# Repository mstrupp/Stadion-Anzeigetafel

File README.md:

# Stadion-Anzeigetafel

## Zusammenfassung

Bei Leichtathletik Wettkämpfen erfolgt die Zeitmessung mit einer elektronischen Zeitmessanlage.
Der Startschuss startet die Stoppuhr und ein Zielbildauswerter bestimmt auf den Zielbildern die Zeiten der Läufer.

Während den Rennen wird auf einer Anzeigetafel die verstrichene Zeit dargestellt.
Außerdem können darauf nach einem Rennen die Zeiten der Läufer angezeigt werden.

In diesem Projekt wird eine Anzeigetafel entwickelt, die mit Zeitmesssystemen der Marke OMEGA kompatibel ist.
Die Anzeige kann eigenständig oder unterstützend eingesetzt werden.
Im eigenständigen Aufbau übernimmt sie alle Aufgaben der Anzeigetafel.
Im unterstützenden Modus werden Zusatzinformationen, wie der Name des Läufers, angezeigt, während eine weitere Anzeigetafel die Zeiten einblendet.

## Technische Daten

Die Namen-Anzeigetafel ist ein LED-Display, das bis zu 12 Buchstaben in einer Zeile anzeigen kann.
Es ist aus einer Distanz von bis zu 75 m lesbar.
Der Benutzer kann zwischen verschiedenen Modi wählen, um den Namen, die Bahn oder die Platzierung anzuzeigen.
Die Helligkeit der Anzeige wird automatisch an die aktuellen Lichtverhältnisse angepasst.
Das regensichere Gehäuse schützt die Elektronik auch bei schlechtem Wetter mit der Schutzklasse IP24.

## Aufbau

### LED Anzeige

Das Display besteht aus einer LED-Matrix.
Dafür werden individuell adressierbare LED-Streifen verwendet. Die LED-Streifen haben eine Dichte von 60 LEDs pro Meter.
Der Pixel-Abstand beträgt etwa 1,7 cm.
Die Anzeige hat eine Auflösung von 83 x 10 Pixeln.
Die Maße der Anzeige betragen etwa 140 x 17 cm.
Jeder Buchstabe ist damit 6 x 10 Pixel bzw. 10 cm x 17 cm groß.

### Mikrocontroller

Die Ergebnis-Daten werden von einem STM Mikrocontroller auf einem Nucleo-32 Board empfangen und aufbereitet.
Die Daten werden von der Zielbildauswertung über die serielle RS422 Schnittstelle bereitgestellt.
Der Mikrocontroller berechnet unter den gegeben Benutzer-Einstellungen die Steuerungssignale für das Display.

### Schnittstellen

Für den Daten-Empfang wird der Data-Out Anschluss der OMEGA-Anzeigetafel verwendet.
Die Verbindung erfolgt über ein Datenkabel mit einem siebenpoligem Tuchel-Anschluss.
Zum Programmieren des Mikrocontrollers ist außerdem ein USB Anschluss am Gehäuse angebracht.

### Automatische Helligkeitsregulierung

Die Helligkeit der Anzeige wird automatisch an die aktuellen Lichtverhältnisse angepasst.
Zur Ermittlung der Umgebungshelligkeit wird ein Fotowiderstand eingesetzt.
Bei starker Sonneneinstrahlung wird zur verbesserten Lesbarkeit die Helligkeit des Displays erhöht.
Bei Dunkelheit wird die Helligkeit verringert.

### Betriebsmodi

Die Anzeigetafel verfügt über verschiedene Betriebsarten.
Es kann entweder der Name oder die Startnummer und die Bahn angezeigt werden.
Über Schalter kann der Bediener auswählen, was angezeigt wird. Ein weiterer Schalter aktiviert das Scrollen von langen Namen, die nicht mit zehn Zeichen dargestellt werden können.
Über ein Potentiometer kann die Helligkeit manuell justiert werden.
Das Ein- und Ausschalten des Geräts ist ebenfalls über einen Schalter möglich.

### Spannungsversorgung

Sowohl der Arduino als auch die LED Streifen benötigen eine elektrische Spannung von 5 V. Diese wird über ein externes Netzteil bereitgestellt.

### Gehäuse

Das Gehäuse besteht aus PVC und bietet damit Schutz vor Regen in der Sicherheitsklasse IP24.
Die Vorderseite besteht aus einer dunklen Plexiglas Scheibe, um die gute Lesbarkeit der Anzeige zu ermöglichen.

## Schaltplan

Zum Einstellen des Modus werden Kippschalter, Potentiometer und Drehschalter verwendet.
Außerdem ermitteln Sensoren die Helligkeit und Temperatur.
Die Komponenten werden auf einer Platine mit dem Mikrocontroller und miteinander verbunden.

[Schaltplan](PCB-Eagle/Anzeigetafel-Schaltplan.pdf)

[PCB](PCB-Eagle/Anzeigetafel-PCB.pdf)

## Steuerung der Anzeige

Die Anzeige besteht aus einer LED-Matrix mit 840 RGB LEDs. Die LEDs sind in Reihen auf LED-Streifen angebracht. Jede einzelne RGB LED besteht aus drei kleinen LEDs in den Farben Rot, Grün und Blau. Durch Kombination der einzelnen Farb-LEDs kann ein breites Farbspektrum erzeugt werden.

### WS2812B RGB LED Streifen

Auf den LED-Streifen sind WS2812B ICs angebracht, die die einzelnen LEDs steuern. Alle ICs sind in Reihe geschaltet. Vom Mikrocontroller werden nacheinander die Farbcodes für die einzelnen LEDs gesendet.

Der erste Chip empfängt das Steuersignal und verarbeitet den ersten Farbcode. Daraufhin enterfernt der IC den ersten Farbcode aus dem Steuersignal und gibt das resultierene Signal an die folgenden Chips weiter.
Die nächsten ICs wiederholen das Vorgehen. Somit wird das Steuersignal von Chip zu Chip kürzer, bis es den letzten Chip erreicht. Am Ende des Steuersignals wird ein Reset-Signal gesendet [3].

Abbildung: Ablauf der WS2812B Steuerung

### Benötigte Signale

Jeder Farbcode besteht aus 24 Bit beziehungsweise 3 Byte. In jedem Byte ist die Intensität einer Farbe enthalten. Im ersten Byte ist der Grünwert, im zweiten der Rotwert und im dritten Byte der Blauwert kodiert. Daraus entstehen drei Werte, die von 0 bis 256 reichen. Diese ergeben den RGB-Wert der LED [3].

Abbildung: Aufbau eines Farbcodes

Die 24 Bit je Farbcode werden elektrisch über ein Datenkabel an die Chips gesendet. Die Spannung auf dem Kabel wird entweder auf "high" oder "low" gesetzt (3,3 V oder 0 V). Je nachdem, wie lange das Signal im Zustand "high" und "low" verbringt, wird es als "0" oder "1" interpretiert. Die genauen Zeitverhältnisse sind in folgender Abbildung dargestellt [3].

Abbildung: Timing der Signale

Die Periode für das Senden einer 0/1-Signals beträgt 1,25 µs. Die high/low-Signale haben eine Toleranz von ±150 ns.

Nachdem die Farbcodes aller LEDs gesendet wurden, folgt ein Reset-Signal. Dazu wird die Datenleitung für mindestens 50 µs auf "low" gebracht [3].

### Erzeugung der Signale

Der Mikrocontroller verfügt über verschiedene Timer. Ein Timer mit PWM (Pulsweitenmodulation) Unterstützung wird für die Erzeugung der Steuersignale verwendet [2].

Die PWM-Periode muss wie gefordert auf 1,25 µs, was einer Frequenz von 800 kHz entspricht, gestellt werden.
Der Timer arbeitet mit einer Frequenz von 64 MHz.
Wenn der Timer innerhalb von einer Periode von 0 bis 79 zählt und dann zurückgesetzt wird, kann die erforderliche Frequenz erreicht werden.

Durch Einstellen des Tastgrades / Duty Cycles kann das Verhältnis von "high" und "low" innerhalb einer Periode geändert werden.

Bei einem Tastgrad von a = 0,32 wird ein "0"-Signal und bei einem Tastgrad von a = 0,64 ein "1"-Signal erzeugt.

#### Direct Memory Access

Der Tastgrad muss also ständig geändert werden.
Wenn die CPU dafür benutzt wird, kann nicht sichergestellt werden, dass das Timing eingehalten wird.
Es würde alle 1,25 µs ein gespeicherter Tastgrad-Wert geladen und ins Timer Register geschrieben werden.
Außerdem ist die CPU somit während dem Senden eines Signals durchgehend ausgelastet und kann nicht auf andere Signale reagieren.

Deshalb wird die DMA (Direct Memory Access) Funktion des Mikrocontrollers eingesetzt.
Diese schafft eine direkte Verbindung zwischen den Speicheradressen der Tastgrade und dem PWM Registers des Timers.
Die CPU startet zu Beginn die DMA-Verbindung.
Dann wird automatisch nach jeder Timer Periode der neue Tastgrad eingestellt [2].

Abbildung: Skizze Direct Memory Access

### Double Buffering

Insgesamt besitzt die Anzeigetafel 840 Pixel.
Wie beschrieben bekommt jeder Pixel ein 24 Bit langes Datensignal.
Für jedes Bit muss der Tastgrad angepasst werden.
Die Tastgrade werden in einem Array gespeichert und dann per DMA an den Timer gegeben.
In dem Array wird jeder Wert als `uint8_t` gespeichert und belegt somit 1 Byte des RAMs.

Das bedeutet, dass das Array eine Speichergröße von 840 * 24 Byte = 20,16 Kilobyte beansprucht.
Das übersteigt die Größe des RAMs des Mikrocontrollers (8 Kilobyte) bei weitem.

Double Buffering wird eingesetzt, um den Speicherbedarf stark zu verringern [4].

Statt ein Array mit allen Tastgraden anzulegen, wird lediglich ein Array mit 48 Einträgen erzeugt.
Dieses bietet Platz für die Tastgrade von genau zwei LEDs.

Der DMA wird im "Circle Mode" konfiguriert.
In diesem Modus sendet er das angegebene Array and die ausgewählte Peripherie und startet dann von vorne.

Dieses Verhalten wird ausgenutzt, um alle LEDs mit dem 48 Byte großen Array anzusteuern.
Zuerst werden die Tastgrade für LED 1 und LED 2 in das Array geladen und der DMA gestartet.
Sobald das Signal für LED 1 generiert wurde, beginnt der DMA, die Tastgrade für LED 2 weiterzugeben.
Währenddessen werden die Tastgrade für LED 1 mit den Tastgraden für LED 3 überschrieben.
Wenn LED 2 gesendet wurde, beginnt der DMA von vorne.
In der ersten Hälfte des Arrays stehen nun die Tastgrade für LED 3 und dadurch wird das dazugehörige Signal generiert.
Das Vorgehen wird wiederholt, bis die Signale für alle LEDs gesendet wurden [4].
Zuletzt wird der Tastgrad auf "0" gesetzt, um das Reset-Signal zu erzeugen.

Abbildung: Ablauf des DMA mit Double Buffering

Der DMA löst Interrupts aus, über die das Tastgrade-Array dann angepasst werden kann.
Wenn die erste Hälfte des Arrays gesendet wurde, wird die Funktion `HAL_TIM_PWM_PulseFinishedHalfCpltCallback` aufgerufen.
Wenn die zweite Hälfte des Arrays gesendet wurde, wird `HAL_TIM_PWM_PulseFinishedCallback` aufgerufen [1].
In diesen Funktionen kann dann das Array mit den neuen Tastgraden befüllt werden.

Abbildung: Auslösen der Interrupts/Callbacks

Die CPU wird beim DMA mit Double Buffering alle 30 µs verwendet.
Damit wird sie 24 Mal weniger belastet als beim Vorgehen ohne DMA.

Das Tastgrade-Array beinhaltet 48 32-Bit Zahlen.
Die Speichergröße beträgt damit 192 Byte.
Dabei spielt es keine Rolle, wie viele LEDs angesteuert werden.
Somit wird im Vergleich zum DMA ohne Double Buffering nur ein Hundertstel des Speicherplatzes verwendet.

## Programm-Repräsentation der LED-Matrix

Um die Verkabelung zu vereinfachen, sind die LEDs im Zickzack auf der Anzeigetafel aufgebrahcht.
In der ersten Zeile läuft das Datensignal daher von links nach rechts, in der zweiten von rechts nach links und so weiter.
Jeder LED wird ein Index, beginnend bei 0, zugeordnet.

Im Programm werden die Farbwerte aller LEDs in einem Array gespeichert.
Die Indizierung unterscheidet sich dadurch in jeder zweiten Zeile, wie in der folgenden Abbildung dargestellt.

Abbildung LED-Matrix und Array Indizierung

Wie zu sehen ist, unterscheiden sich die Indizierung der realen LED-Matrix und die des Arrays in jeder zweiten Zeile.
Um die Buchstaben und Zahlen trotzdem lesbar anzuzeigen, muss der Programmcode entsprechend angepasst werden.

### Programm eines Buchstaben, einer Zahl oder anderen Zeichens

Jedes Zeichen, das angezeigt werden soll, besteht aus einer Matrix.
Diese gibt an, welche LEDs für dieses Zeichen an- und ausgeschaltet werden sollen.

```C
const Character char0x41 = { // A
        .width = 6,
        .height = 10,
        .matrix = {
                0, 0, 1, 1, 0, 0,
                0, 1, 0, 0, 1, 0,
                1, 0, 0, 0, 0, 1,
                1, 0, 0, 0, 0, 1,
                1, 0, 0, 0, 0, 1,
                1, 1, 1, 1, 1, 1,
                1, 0, 0, 0, 0, 1,
                1, 0, 0, 0, 0, 1,
                1, 0, 0, 0, 0, 1,
                1, 0, 0, 0, 0, 1
        }
};
```

Listing: Code für den Buchstaben A

### Programm zum Füllen der LED-Matrix

Folgender Code wird dann zum Füllen des Arrays verwendet.

```C
// Set a character at the current cursor position in the given color.
void LEDMatrixSetCharacter(LEDMatrix* ledMatrix, const Character* character, Color color) {
    int currentCursorPos;;
    // Iterate over all character cells
    for (int line = 0; line < character->height; ++line) {
        currentCursorPos = ledMatrix->cursorPos;
        for (int col = 0; col < character->width; ++col) {
            // Check if the column is inside the matrix
            if (currentCursorPos >= 0 && currentCursorPos < ledMatrix->numCols) {
                // Even line: LEDs from left to right
                if (line % 2 == 0) {
                    ledMatrix->leds[line * ledMatrix->numCols + col + ledMatrix->cursorPos].color =
                            character->matrix[line * character->width + col] ? color : off;
                // Uneven line: LEDs from right to left
                } else {
                    ledMatrix->leds[line * ledMatrix->numCols + (ledMatrix->numCols - 1 - col) - ledMatrix->cursorPos].color =
                            character->matrix[line * character->width + col] ? color : off;
                }
            }
            currentCursorPos += 1;
        }
    }
}
```

Listing: Code zum Hinzufügen eines Buchstaben zur Matrix

An die Funktion werden die LED-Matrix, das neue Zeichen und die Farbe übergeben.
Es wird über jede Zelle der Buchstaben-Matrix iteriert.
Wenn die berechnete Zelle innerhalb der LED-Matrix liegt, wird die zugehörige LED angeschaltet.
Mithilfe von `if (line $ 2 == 0)` wird getestet, ob die Zeile gerade oder ungerade ist.
Wie zuvor beschrieben wird dementsprechend die Beschreibe-Richtung der LED-Matrix angepasst.
Beim Setzen der LED wird dann außerdem die Farbe dieser LED festgelegt.

### Animationen

Unter Benutzung eines weiteren Timers ist es möglich, Animationen auf der Anzeigetafel abzuspielen.
Der Quellcode dafür befindet sich im Ordner `animations`.
Die Animation `SwipeClearAnimation` lässt zum Beispiel einen Streifen von links nach rechts über die Anzeige wischen, der dabei all Zeichen löscht.

Bei Animationen ist zu beachten, dass die Aktualisierungsrate der Anzeige von der Anzahl der LEDs abhängt.
Die Signallänge jedes Bits 1,25 µs.
Für jede LED werden 24 Bit gesendet.
Nach dem Senden aller LED-Signale folgt ein Reset-Puls mit einer Dauer von 50 µs.
Die benötigte Zeit zum Senden eines gesamten Bildes ergibt sich damit zu

`T = n * 24 * 1,25 µs + 50 µs`,
wobei `n` die Anzahl der LEDs ist.

Für die im Projekt verwendeten n = 830 LEDs ergibt sich damit eine Sendezeit von 24,95 ms.
Damit liegt die theoretisch mögliche Aktualisierungsrate bei etwa 4 Bildern pro Sekunde.

## Empfang der Daten

Die Anzeige-Befehle werden über die RS422 Schnittstelle bereitgestellt.
Der MAX485 IC leitet die Daten als für den Mikrocontroller lesbares Signal weiter.
Es gibt verschiedene Protokolle, in denen die Informationen empfangen werden können.
Das Projekt unterstützt das Gemini sowie das Rollertime Protokoll.
Die Dekodierunds-Funktionen sind in den Quelldateien im Ordner `protocols` implementiert.

In den Dekodierungs-Funktionen werden die empfangenen Daten anylisert und geprüft, um welchen Datentyp es sich handelt.
Im Gemini Protokoll kann zum Beispiel enthalten sein:

- Aktuelle Zeit
- Name eines Athleten
- Ergebnis eines Athleten
- Startnummer eines Athleten
- Bahn eines Athleten
- Platzierung eines Athleten
- Clear-Kommando

Je nach empfangenem Signal wird dann entschieden, was auf der Anzeige dargestellt werden soll und die LED-Signale generiert und versendet.

## Gamma Korrektur

```text
corrected = ((value / 255) ^ gamma) * 255
```

Als Gamma Wert wird 2,5 benutzt.

## Referenzen

[1] STMicroelectronics, Description of STM32G0 HAL and low-layer drivers - User manual. 10-2020.

[2] STMicroelectronics, STM32G0x1 advanced Arm®-based 32-bit MCUs - Reference manual. 11-2020.

[3] Worldsemi, WS2812B Datenblatt. 2021.

[4] M. Tilen, “Tutorial: Control WS2812B leds with STM32,” 2018-06-03. <https://stm32f4-discovery.net/2018/06/tutorial-control-ws2812b-leds-stm32/>

[5] Maxim Integrated, MAX485 Datenblatt. 9-2014.

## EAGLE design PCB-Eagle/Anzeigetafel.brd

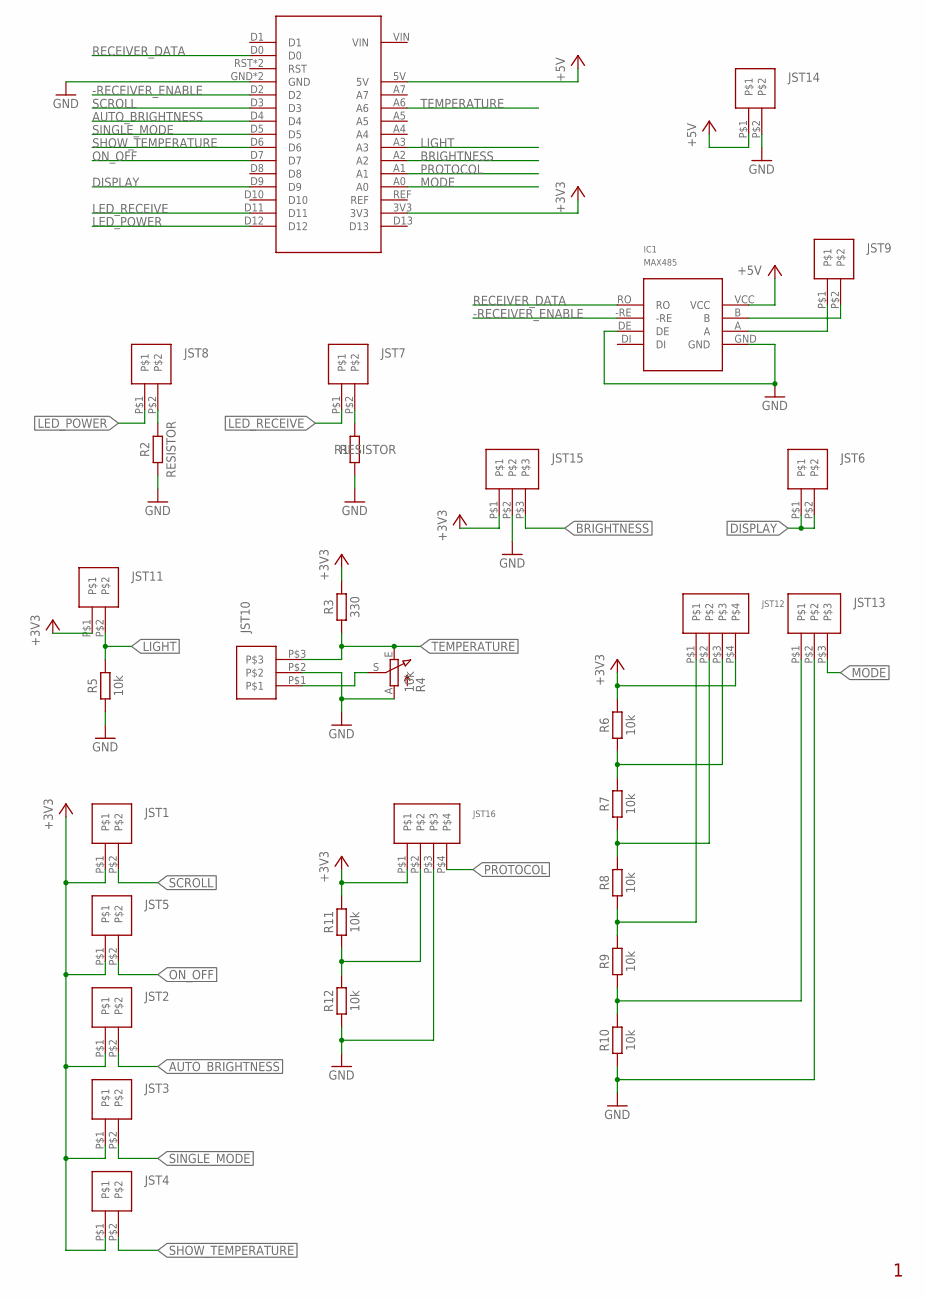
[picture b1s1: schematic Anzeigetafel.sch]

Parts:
IC1: MAX485
JST1, JST2, JST3, JST4, JST5, JST6, JST7, JST8, JST9, JST11, JST14: JST-2
JST10, JST13, JST15: JST-3
JST12, JST16: JST-4
MCU1: NUCLEO-32G0
R1, R2: RESISTOR; 0207/7
R3: 330; 0207/7
R4: 10k; S64W
R5, R6, R7, R8, R9, R10, R11, R12: 10k; 0207/7

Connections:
+3V3: JST1.P$1, JST2.P$1, JST3.P$1, JST4.P$1, JST5.P$1, JST11.P$1, JST12.P$4, JST15.P$1, JST16.P$1, MCU1.3V3, R3.2, R6.2, R11.2
+5V: IC1.VCC, JST14.P$1, MCU1.5V
-RECEIVER_ENABLE: IC1.-RE, MCU1.D2
AUTO_BRIGHTNESS: JST2.P$2, MCU1.D4
BRIGHTNESS: JST15.P$3, MCU1.A2
DISPLAY: JST6.P$1, JST6.P$2, MCU1.D9
GND: IC1.DE, IC1.GND, JST10.P$2, JST13.P$2, JST14.P$2, JST15.P$2, JST16.P$3, MCU1.GND, MCU1.GND1 (GND), R1.1, R2.1, R4.A, R5.1, R10.1, R12.1
LED_POWER: JST8.P$1, MCU1.D12
LED_RECEIVE: JST7.P$1, MCU1.D11
LIGHT: JST11.P$2, MCU1.A3, R5.2
MODE: JST13.P$3, MCU1.A0
unnamed: JST8.P$2, R2.2
unnamed: IC1.A, JST9.P$1
unnamed: JST7.P$2, R1.2
unnamed: JST10.P$1, R4.S
unnamed: IC1.B, JST9.P$2
unnamed: JST12.P$3, R6.1, R7.2
unnamed: JST12.P$2, R7.1, R8.2
unnamed: JST12.P$1, R8.1, R9.2
unnamed: JST13.P$1, R9.1, R10.2
unnamed: JST16.P$2, R11.1, R12.2
ON_OFF: JST5.P$2, MCU1.D7
PROTOCOL: JST16.P$4, MCU1.A1
RECEIVER_DATA: IC1.RO, MCU1.D0
SCROLL: JST1.P$2, MCU1.D3
SHOW_TEMPERATURE: JST4.P$2, MCU1.D6
SINGLE_MODE: JST3.P$2, MCU1.D5
TEMPERATURE: JST10.P$3, MCU1.A6, R3.1, R4.E

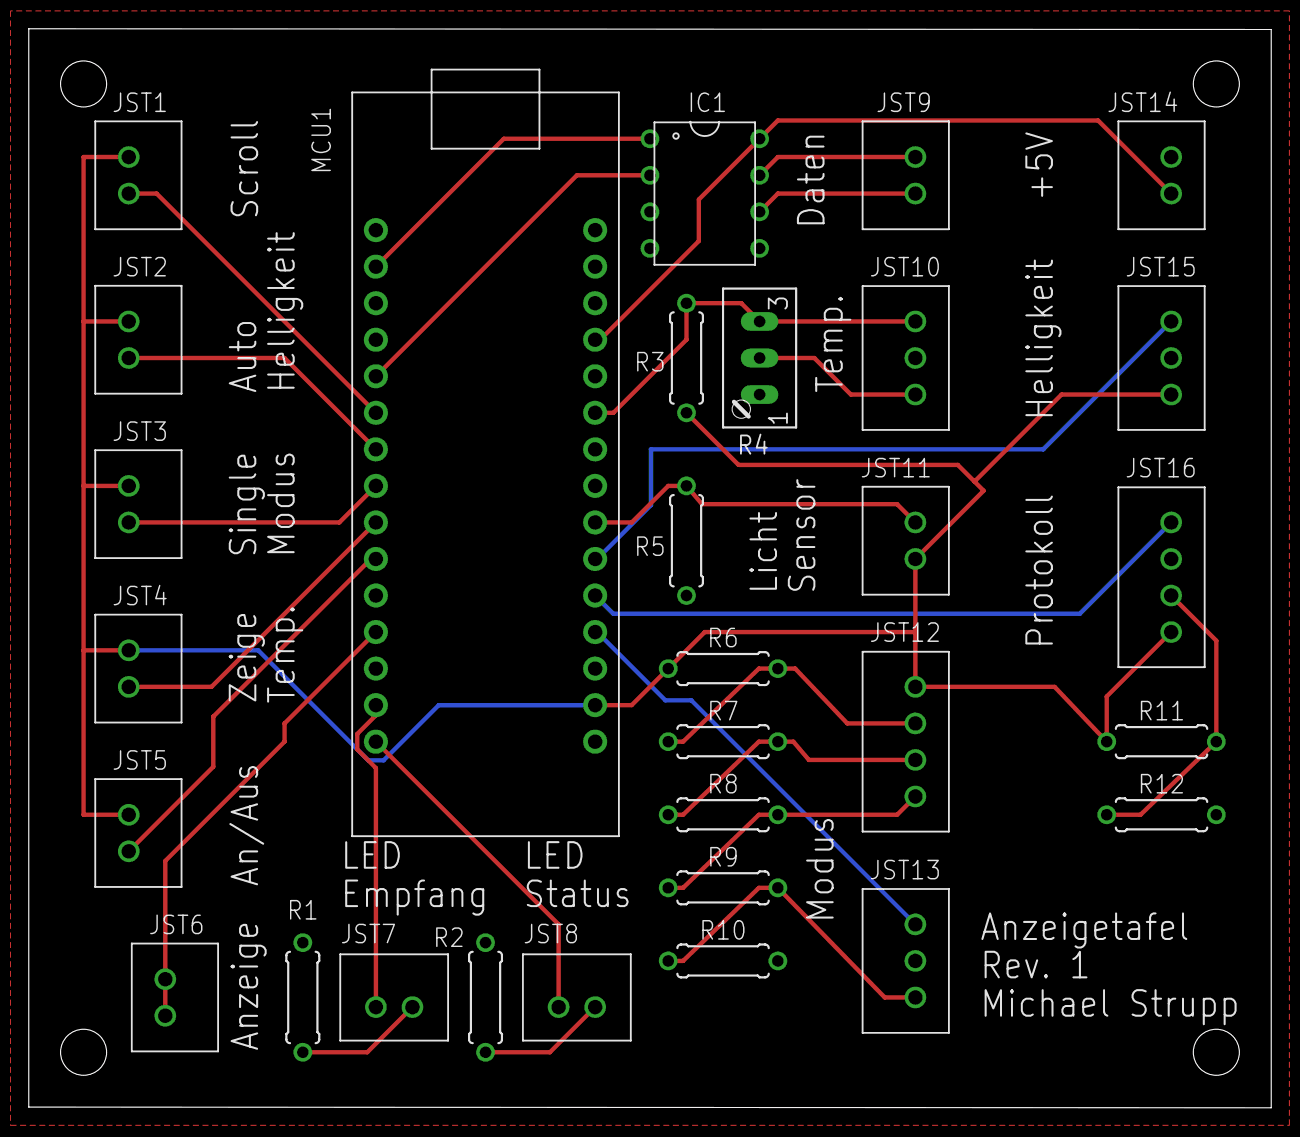
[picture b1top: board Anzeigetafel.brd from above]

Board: 2 copper layers, 86.4 x 75.0 mm, 30 parts (0 on the bottom side), 28 nets.

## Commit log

2021-09-23 Inital Commit
2021-09-24 Added led control functions - LED stores the information about single LEDs - LEDMatrix stores the whole array of LEDs, LED pattern logic and PWM generation functions.
2021-09-24 Added code for PWM generation - Send buffer using DMA callbacks - Including example code
2021-09-24 Fixed LED initialization - Call the init function
2021-09-24 Improved documentation
2021-09-24 Bugfix
2021-09-24 Increased maximum number of LEDs - From uint8_t (256) to uint32_t (more than enough)
2021-09-27 Started led control documentation
2021-09-30 Small improvements - Option to change duty cycles to use other ICs than WS2812B - Added color amber - Improved example code, now possible to use more LEDs
2021-09-30 Added white color, small changes - Enabled WS2812B timing instead WS2811
2021-09-30 Added matrix manipulation functions - Added font.h where all characters will be stored - Added test character letterA - Added matrix clear function - Added set matrix character test function - Introd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
2021-10-01 Added function to set a string to the LED matrix - Added LEDMatrixAddText function - Added getCharacter function that matches a char to a Character
2021-10-01 Added aligntment - Set the alignment with LEDMatrixSetAlignment to left, center, right or append
2021-10-01 Avoid pixel overflows in matrix to the left and to the right - Adds support for negative cursor positions
2021-10-01 Added Animation capability - Added SwipeClearAnimation as example - Moved Character from font to own file - Moved font.h and font.c in fonts folder - Made LEDMatrixSetCharacter public - Set up Timer 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
2021-10-02 Documentation: Added Signal Generation chapter
2021-10-04 Added Double Buffering documentation
2021-10-04 Documentation improvements - Replaced png with svg files, better resolution - Added references
2021-10-04 Documentation: Added project description
2021-10-07 Added functions to read and process RS485 control messages from the photofinish PC
    - Enabled the microcontroller uart
    - RS485Receiver handles the uart and checks for messages
    - Message is a struct that can save all relevant information of a received message
    - geminiGenerateMessage and rollertimeGenerateMessage convert the received strings to Message structs according to the corresponding protocols
    - Scoreboard is the top level function that will control the complete system.
    ScoreboardMain is called when a new serial message is received. The new matrix output will then be determined and sent to the LEDs.
2021-10-22 Minor improvements
    - Added debug color (very dim color that does not hurt your eyes while debugging)
    - Bugfix in gemini receive protocol
2021-10-22 Receive RS422 commands and various improvements
    - Process and display basic commands from photofinish PC
    - Added complete alphabet and numbers to font.
    - LEDMatrix now checks if a code is currently being sent. Don't accept new send requests while sending.
    - Made SwipeClearAnimation compatible with 10 pixel high led matrix.
    - Increased matrix send timer interrupt priority
2021-10-22 Documentation: Added Matrix Code chapter
    - Minor typo fixes
2021-10-22 Documentation: Added data receiving and animations chapter
2022-01-06 Added PCB design files
2022-01-06 Improved documentation
    - Added circuit diagram
2022-01-06 Added circuit diagram image in documentation
2022-01-06 Added images to the documentation
2022-09-08 General refinements for first in-practice test
    - Added competition code
    - Added colors
    - Added settings logic by clear command
    - Added letters
2022-09-08 Added Scroll Animation
2022-09-08 Added Temperature Sensor
2023-04-15 Adjustments for Flutlichtmeeting 2022
2023-04-15 Updated CubeIDE
2023-04-15 Optimization and recalculation
    - Reduce reset time to 72 us
    - Corrected max FPS calculation
2023-04-15 Scroll Animation Bugfix
    - Dynamically allocate array of leds
    - Fixed display glitch when scroll animation repeats
2023-04-16 Various Improvements
    - Added show requests: Show later if matrix is currently sending
    - Fixed Scroll Animation
    - Small fix in swipe clear animation
    - Preparations for WHS 2023
